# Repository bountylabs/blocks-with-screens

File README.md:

# Blocks With Screens

It's Twitterversary blocks, but with screens and internet. Originally a Fall 2019 Twitter HackWeek project by [@johnboiles](https://github.com/johnboiles), [@magus](https://github.com/magus), [@mikeperiscope](https://github.com/mikeperiscope), [@seanfchan](https://github.com/seanfchan), and [@smartfuse](https://github.com/smartfuse).

## Assembly

### [**Click here to view assembly instructions on YouTube**](https://youtu.be/LxgdhXQPZw0)

Tips, notes & corrections:
* To protect the pins, we're shipping with two of the circuit boards attached to eachother. You'll need to separate these circuit boards before following the instructions above. Just gently pull them apart to separate them. They're hard to break :)
* Some of the boards may have small tabs protruding from the sides which may cause them not to fit in the wooden block. This is a byproduct of the manufacturing process. Clip these tabs off with nail clippers or wire clippers.
* Feel free to ask us on Twitter [@blkswithscreens](https://twitter.com/blkswithscreens) if you have any questions or problems!

## Components

### Blockware

This is the example software that you can run on the blocks. See [blockware/README.md](https://github.com/bountylabs/blocks-with-screens/blob/main/blockware/README.md) for installation instructions and a listing (with gifs!) of the available blockware.

### CAD

This contains the various design files building the block hardware. Most importantly, it contains the [Autodesk Eagle](https://www.autodesk.com/products/eagle/free-download) design files for the 3 PCBs that make up the block. See the [README.md](https://github.com/bountylabs/blocks-with-screens/blob/main/cad/pcb/README.md) in that directory for an overview of the responsibilities of the three different boards.

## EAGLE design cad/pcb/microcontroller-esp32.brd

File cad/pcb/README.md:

# Blocks With Screens PCB Files

## Components

The blocks are made up of 3 components.

### OLED Board

This board is responsible for all the circuitry to drive a SSD1351 OLED display. This design is heavily based on [Adafruit's breakout board](https://github.com/adafruit/Adafruit-1.5inch-Color-OLED-PCB) for the same display.

It consists of a 13V boost regulator to provide the required voltage to drive the OLED, as well as necessary passive components required by the OLED's datasheet.

### Microcontroller Board

This board is a mounting point for the ESP12 microcontroller and the MMA8452Q 3-axis accelerometer. It also has unpopulated pads for a [SparkFun Qwiic](https://www.sparkfun.com/qwiic) connector and a WS2812B RGB LED if you want to add additional functionality.

### USB Board

This board is responsible for:
* Providing a USB serial interface for programming the microcontroller (with automatic reset)
* Providing regulated 3.3V power to the Microcontroller and OLED
* Providing charging circuitry to charge the LiPo battery

This board is based on various Adafruit [LiPo charging boards](https://learn.adafruit.com/adafruit-pro-trinket-lipoly-slash-liion-backpack) and [USB powered boards](https://learn.adafruit.com/introducing-trinket/downloads) with the simplest (by part count) USB-serial chip we could find.

## PCB Hacking

We hope you'll open up your blocks and add new functionality or boards we never even dreamed of.

The pin layout is compatible with the [Wemos D1 Mini](https://docs.wemos.cc/en/latest/d1/d1_mini.html) (available on your usual internet shopping sites) so any shields made for those should work!

There is un unpopulated [SparkFun Qwiic](https://www.sparkfun.com/qwiic) connector on the microcontroller board. If you solder on a Qwiic connector (just a 4-pin JST connector) you can connect your board to any of the dozens of [Qwiic compatible peripherals](https://www.sparkfun.com/qwiic#products) (e.g. sensors, screens, GPS) out there.

There's an unpopulated spot on the Microcontroller board for a WS2812B RGB LED (or similar). This might come in handy if you want to, say, cut a window in the side of your block and trick it out with colors inside. Note that these LEDs will typically initialize to a random color so if you add the LED, but don't use it in your program, it will probably be lit up to a random color.

You could also add PCBs for different microcontrollers, different screens, or maybe even make a USB-C version! This was meant to be modular. Have fun, and share back what you build!

## Manufacturing Boards

We used [OshPark](https://oshpark.com/) for creating our prototype PCBs which we then soldered by hand or in a [reflow oven](https://github.com/UnifiedEngineering/T-962-improvements). We used [PCBWay](https://www.pcbway.com/) to mass manufacture assembled PCBs.

There's an included [script](https://github.com/bountylabs/blocks-with-screens/blob/main/pcb/eagle_to_pcbway.py) for exporting the Eagle PCB files in a bill-of-materials (BOM) format that PCBWay accepts.

## Changelog

### Microcontroller Board V4

* MMA8452QR1 accelerometers are #chipshortage'd. Switch to LIS2DW12

### OLED Board V5

* Revert the revert to go back to VIN for the 13V boost circuit as it didn't seem to have any effect. And this lightens the load on the 3.3V regulator. This is effectively the same design as OLED Board V3.

### USB Board V5

* Turn the battery connector counter-clockwise by 90 degrees to avoid wires hanging off the side of the board and not fitting in the block.

### OLED Board V4

* Revert back to using 3.3V for the 13V boost circuit to hopefully avoid issues I've seen twice now with the OLED screens developing bad vertical lines of pixels. This is what Adafruit does in their board; perhaps there's a reason for it.

### USB Board V4

* Use thicker (power) trace for 3.3V
* Make the USB side slots wider to comply with PCBWay
* Add a JST-SH connector (SM02B-SRSS-TB) for the battery

### Microcontroller Board V3

* Attach 3.3V to the ESP12 (doh!)

### OLED Board V3

* Uses `D4/GPIO2` for `OLED DC` instead of `D1/GPIO5` since that pin is I2C `SCK`.

### Microcontroller Board V2

* Fixed disconnected decoupling capacitor.
* Added optional header for MMA8452QR1 accelerometer.
* Added optional [Qwiic](https://www.sparkfun.com/qwiic) header for SparkFun accessories.
* Added optional [5050 NeoPixel](https://www.adafruit.com/product/1655) pad.

### USB Board V3

* Fix width of power trace going to the switch.

### OLED Board V2

* Uses `D1` for `OLED DC` instead of `D6` (`MISO`) so we don’t have to hack SPI.c for hardware SPI.
* Uses `VIN` for power for the 13V boost (possible this will reduce the flicker, especially during low battery).
* Removed the 3-pin SPI jumper since we didn’t use it.
* Move all the screen capacitors closer to the screen connector (even smaller chance of reducing flicker)

### USB Board V2

* Removed oscillator and move to using the `CH340C` instead of `CH340G` USB-UART chip.
* Connect `VCC` on the `CH340C` chip (fix error from V1).
* Move most parts to the front of the board for easier manufacturing.
* Add an optional on LED.
* Add pads for a switch.

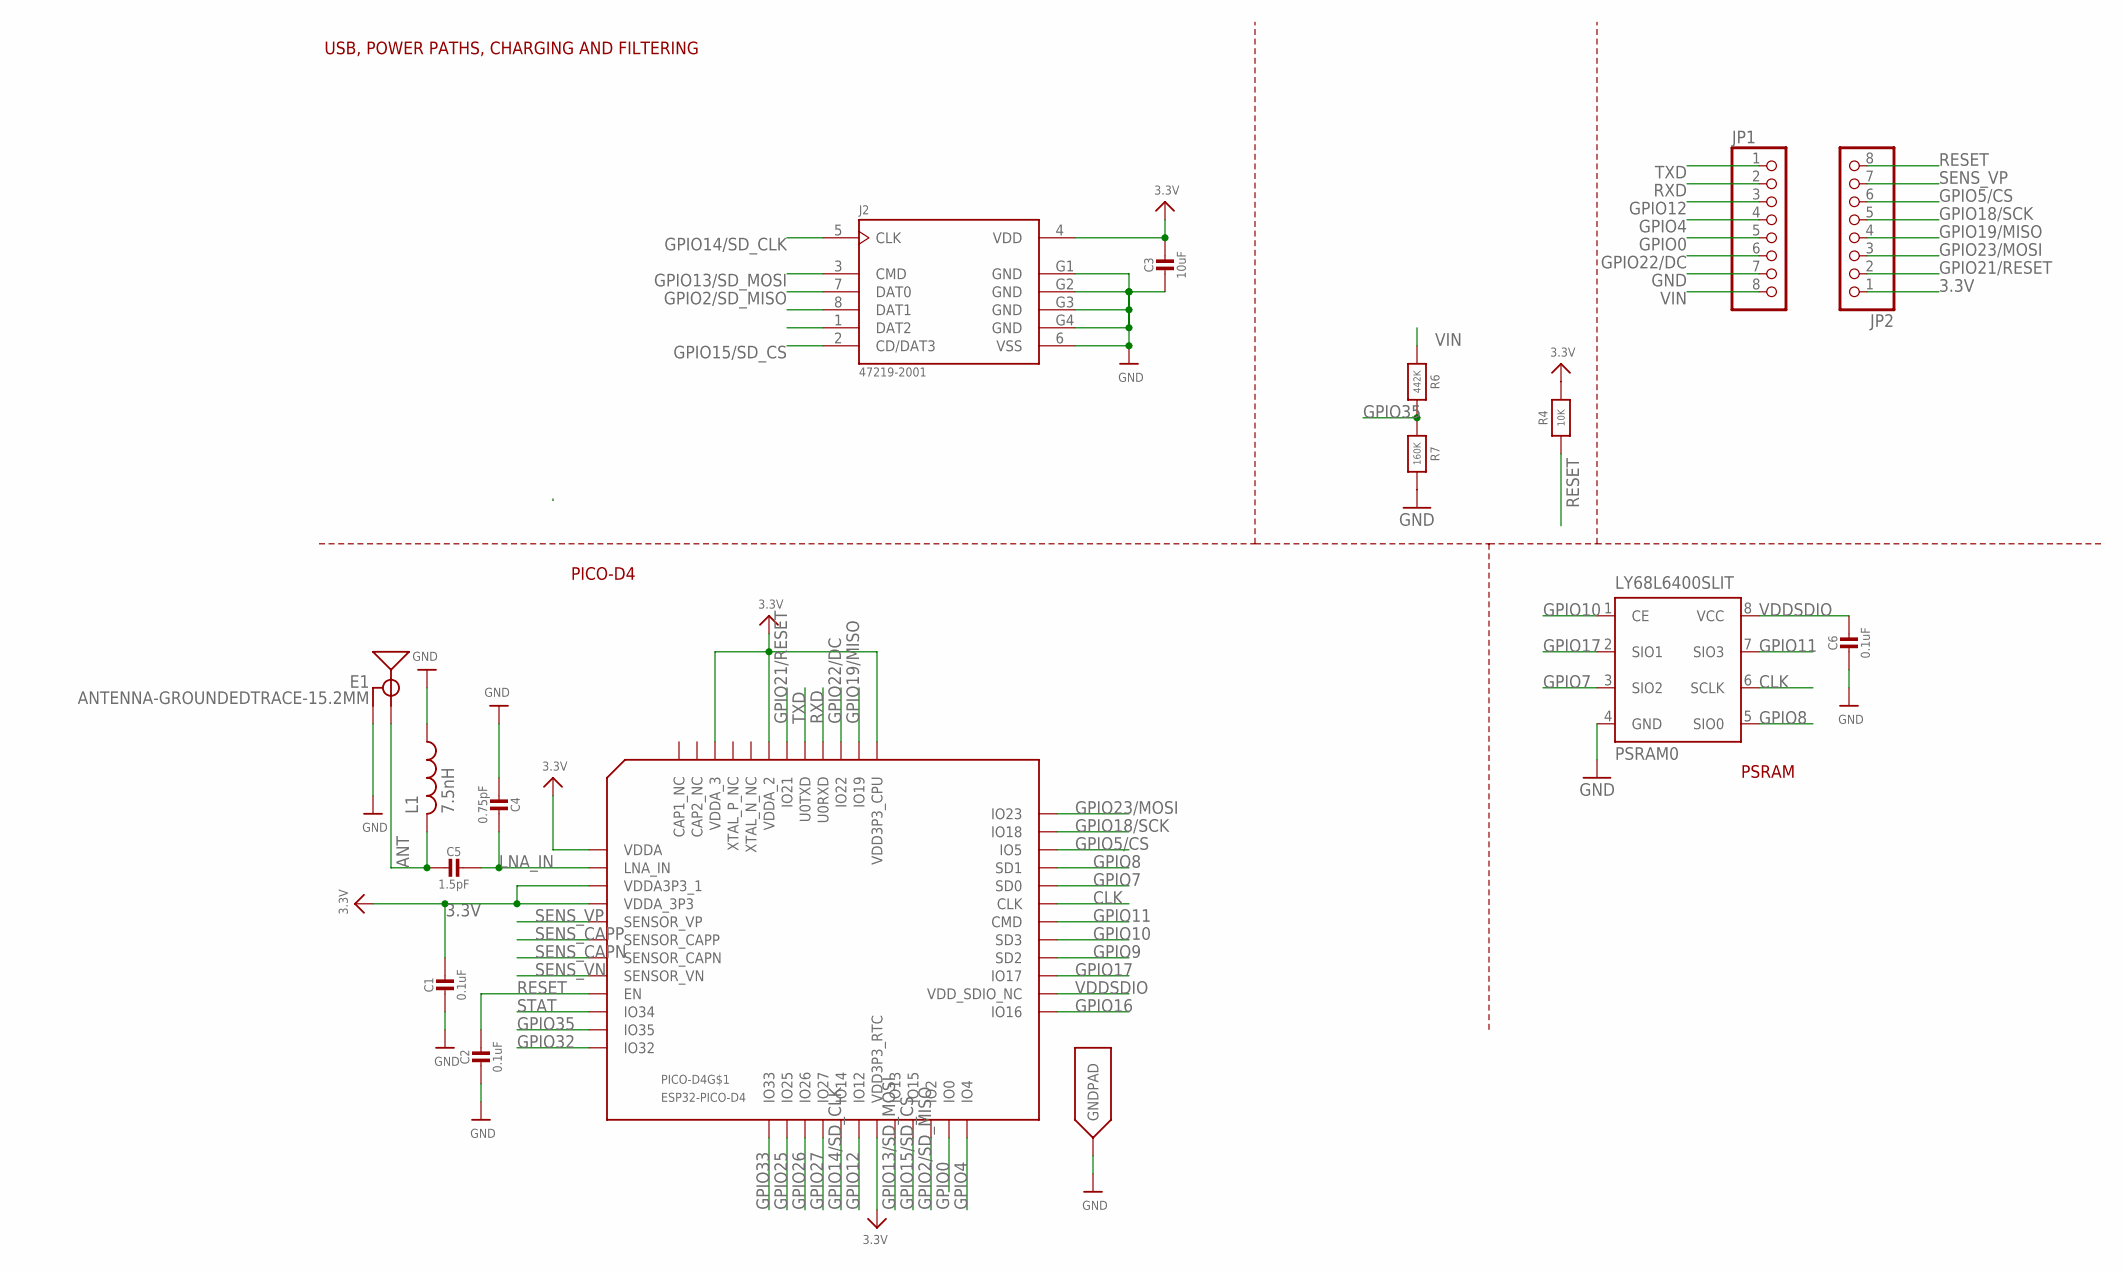
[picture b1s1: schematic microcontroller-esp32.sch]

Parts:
C1, C2, C6: 0.1uF; _0402MP
C3: 10uF; _0402MP
C4: 0.75pF; _0402MP
C5: 1.5pF; _0402MP
E1: ANTENNA-GROUNDEDTRACE-15.2MM; TRACE_ANTENNA_2.4GHZ_15.2MM
J2: 47219-2001; MOLEX_47219-2001
JP1, JP2: PINHD-1X8CLEANBIG; 1X08-CLEANBIG; MPN 83-15410
L1: 7.5nH; RESC0402_N
LY68L6400SLIT: PSRAM0; SOP8
PICO-D4: ESP32-PICO-D4; PICO-D4-QFN48
R4: 10K; _0402MP
R6: 442K; _0402MP
R7: 160K; _0402MP

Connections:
3.3V: C1.1, C3.1, J2.4 (VDD), JP2.1, PICO-D4.1 (VDDA), PICO-D4.3 (VDDA3P3_1), PICO-D4.4 (VDDA_3P3), PICO-D4.19 (VDD3P3_RTC), PICO-D4.37 (VDD3P3_CPU), PICO-D4.43 (VDDA_2), PICO-D4.46 (VDDA_3), R4.2
ANT: C5.2, E1.ANT (SIGNAL), L1.2
CLK: LY68L6400SLIT.6 (SCLK), PICO-D4.31 (CLK)
GND: C1.2, C2.2, C3.2, C4.2, C6.2, E1.GND, J2.6 (VSS), J2.G1 (GND), J2.G2 (GND), J2.G3 (GND), J2.G4 (GND), JP1.7, L1.1, LY68L6400SLIT.4 (GND), PICO-D4.EXP (GNDPAD), R7.2
GPIO0: JP1.5, PICO-D4.23 (IO0)
GPIO2/SD_MISO: J2.7 (DAT0), PICO-D4.22 (IO2)
GPIO4: JP1.4, PICO-D4.24 (IO4)
GPIO5/CS: JP2.6, PICO-D4.34 (IO5)
GPIO7: LY68L6400SLIT.3 (SIO2), PICO-D4.32 (SD0)
GPIO8: LY68L6400SLIT.5 (SIO0), PICO-D4.33 (SD1)
GPIO9: PICO-D4.28 (SD2)
GPIO10: LY68L6400SLIT.1 (CE), PICO-D4.29 (SD3)
GPIO11: LY68L6400SLIT.7 (SIO3), PICO-D4.30 (CMD)
GPIO12: JP1.3, PICO-D4.18 (IO12)
GPIO13/SD_MOSI: J2.3 (CMD), PICO-D4.20 (IO13)
GPIO14/SD_CLK: J2.5 (CLK), PICO-D4.17 (IO14)
GPIO15/SD_CS: J2.2 (CD/DAT3), PICO-D4.21 (IO15)
GPIO16: PICO-D4.25 (IO16)
GPIO17: LY68L6400SLIT.2 (SIO1), PICO-D4.27 (IO17)
GPIO18/SCK: JP2.5, PICO-D4.35 (IO18)
GPIO19/MISO: JP2.4, PICO-D4.38 (IO19)
GPIO21/RESET: JP2.2, PICO-D4.42 (IO21)
GPIO22/DC: JP1.6, PICO-D4.39 (IO22)
GPIO23/MOSI: JP2.3, PICO-D4.36 (IO23)
GPIO25: PICO-D4.14 (IO25)
GPIO26: PICO-D4.15 (IO26)
GPIO27: PICO-D4.16 (IO27)
GPIO32: PICO-D4.12 (IO32)
GPIO33: PICO-D4.13 (IO33)
GPIO35: PICO-D4.11 (IO35), R6.2, R7.1
LNA_IN: C4.1, C5.1, PICO-D4.2 (LNA_IN)
RESET: C2.1, JP2.8, PICO-D4.9 (EN), R4.1
RXD: JP1.2, PICO-D4.40 (U0RXD)
SENS_CAPN: PICO-D4.7 (SENSOR_CAPN)
SENS_CAPP: PICO-D4.6 (SENSOR_CAPP)
SENS_VN: PICO-D4.8 (SENSOR_VN)
SENS_VP: JP2.7, PICO-D4.5 (SENSOR_VP)
STAT: PICO-D4.10 (IO34)
TXD: JP1.1, PICO-D4.41 (U0TXD)
VDDSDIO: C6.1, LY68L6400SLIT.8 (VCC), PICO-D4.26 (VDD_SDIO_NC)
VIN: JP1.8, R6.1

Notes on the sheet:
USB, POWER PATHS, CHARGING AND FILTERING
PICO-D4
PSRAM

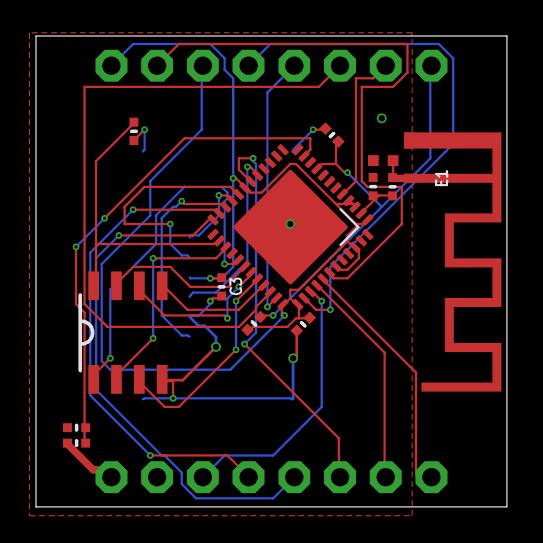
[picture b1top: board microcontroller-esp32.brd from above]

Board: 4 copper layers, 26.2 x 26.2 mm, 16 parts (1 on the bottom side), 30 nets.

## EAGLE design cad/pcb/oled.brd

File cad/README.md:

# CAD Files

This contains the various design files for the mechanical components of the blocks.

## Parts List
* Assembled PCBs (See the README.md in the `pcb` directory in the repository for more details)
  * USB board
  * Microcontroller board
  * OLED board
* 1.5” SSD1351 128x128 OLED screen
* 240mAh 602025 LiPo battery with JST-SH connector
* Laser-cut wood “puzzle” blocks (5 separate pieces that fit together)
* Laser cut paper spacers (for friction fit and alignment)

## Components

### PCBs

The most important part of the block! The `pcb` directory contains the [Autodesk Eagle](https://www.autodesk.com/products/eagle/free-download) design files for the 3 PCBs that make up the block. See the [README.md](https://github.com/bountylabs/blocks-with-screens/blob/main/cad/pcb/README.md) in that directory for an overview of the responsibilities of the three different boards.

### Laser-cut Wood “Puzzle” Blocks

These are the laser-cuttable sides and back of the block. Since these need to fit together with only friction, the design may need to be adjusted based on the laser being used. Designs are included for a 0.23mm kerf laser as well as ones that worked well on @johnboiles's GlowForge. The `puzzleblock.f3d` (Fusion 360) file has the original designs.

### Laser-cut Paper Spacers

These help hold the PCBs inside the block and also helps center them inside the block. These should be cut out of 110 lb card stock paper. The laser width doesn’t matter here since paper bends.

### Block With Screen F3Z File

This Fusion 360 file has all of the components modeled in one place. Used mostly for neat visualizations like the assembly video. Also very useful to visualize the internal spacing when changing PCB components placements. This also contains the original design for the paper spacers.

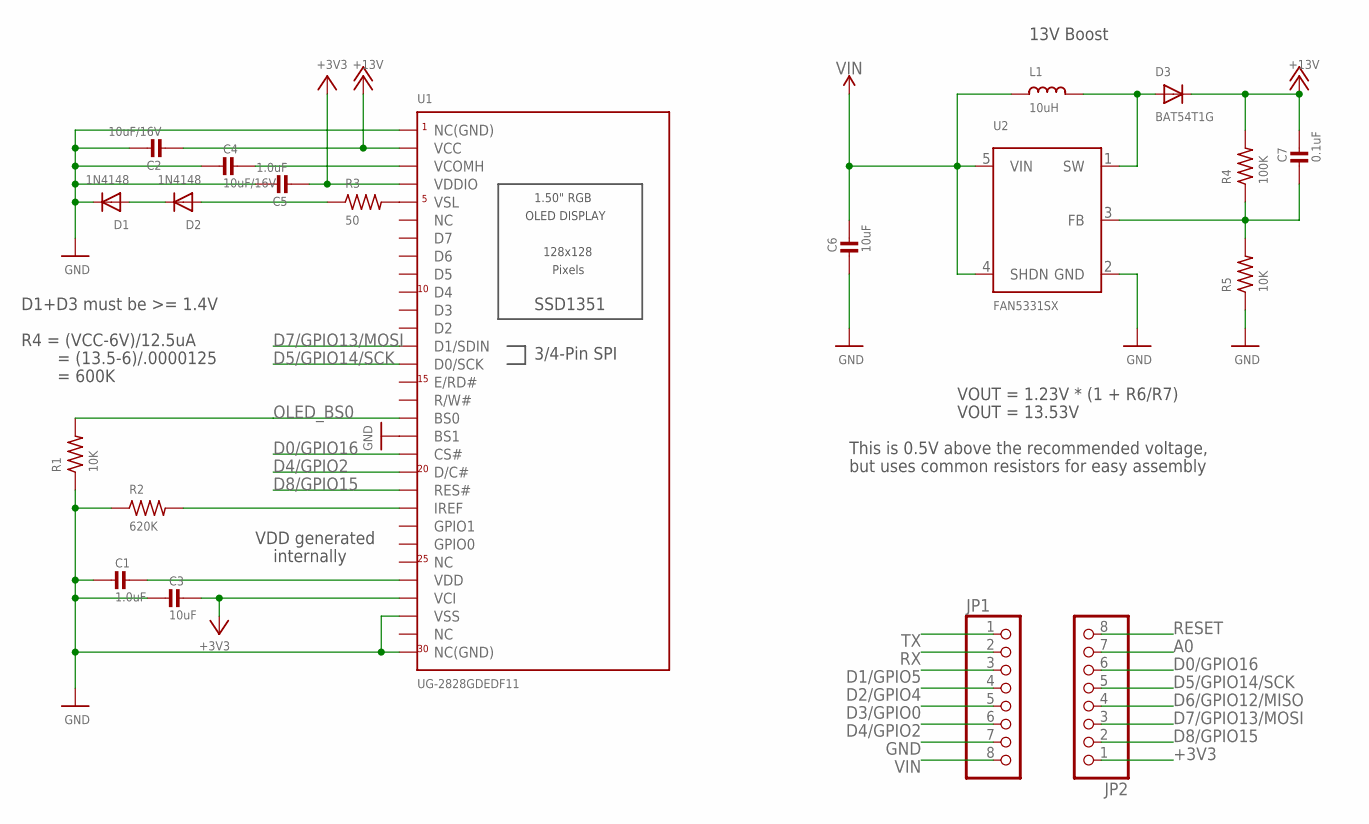
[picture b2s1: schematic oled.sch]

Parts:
C1, C5: 1.0uF; 0805; MPN C0805C105K4RAC7210
C2, C4: 10uF/16V; 0805; MPN CL21A106KOQNNNE
C3, C6: 10uF; 0805; MPN CL21A106KOQNNNE
C7: 0.1uF; 0805; MPN C0805C104M3RACTU
D1, D2: 1N4148; SOD-323; MPN 1N4148WS-E3-08
D3: BAT54T1G; SOD-123; MPN BAT54T1G
JP1, JP2: PINHD-1X8CLEANBIG; 1X08-CLEANBIG; MPN C124381
L1: 10uH; INDUCTOR_1007; MPN L0805R100MPWRT
R1, R5: 10K; R0805; MPN CRCW080510K0FKEAC
R2: 620K; R0805; MPN 0805W8F6203T5E
R3: 50; R0805; MPN CRCW080550R0FKTA
R4: 100K; R0805; MPN CR0805AFX-1003EAS
U1: UG-2828GDEDF11; FPC_XF2M-3015-1A; MPN XF2M-3015-1A
U2: FAN5331SX; SOT23-5@1; MPN FAN5331SX

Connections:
13V: C2.2, C7.1, D3.C, R4.2, U1.P$29 (VCC)
+3V3: C3.1, C5.2, JP2.1, U1.P$4 (VCI), U1.P$27 (VDDIO)
A0: JP2.7
D0/GPIO16: JP2.6, U1.P$12 (CS#)
D1/GPIO5: JP1.3
D2/GPIO4: JP1.4
D3/GPIO0: JP1.5
D4/GPIO2: JP1.6, U1.P$11 (D/C#)
D5/GPIO14/SCK: JP2.5, U1.P$17 (D0/SCK)
D6/GPIO12/MISO: JP2.4
D7/GPIO13/MOSI: JP2.3, U1.P$18 (D1/SDIN)
D8/GPIO15: JP2.2, U1.P$10 (RES#)
GND: C1.2, C2.1, C3.2, C4.2, C5.1, C6.2, D1.C, JP1.7, R1.1, R2.1, R5.1, U1.P$1 (NC(GND)), U1.P$3 (VSS), U1.P$13 (BS1), U1.P$30 (NC(GND)), U2.2 (GND)
IREF: R2.2, U1.P$9 (IREF)
unnamed: C1.1, U1.P$5 (VDD)
unnamed: D3.A, L1.P$2 (2), U2.1 (SW)
unnamed: R3.2, U1.P$26 (VSL)
unnamed: D2.A, R3.1
unnamed: C7.2, R4.1, R5.2, U2.3 (FB)
unnamed: D1.A, D2.C
OLED_BS0: R1.2, U1.P$14 (BS0)
RESET: JP2.8
RX: JP1.2
TX: JP1.1
VCOMH: C4.1, U1.P$28 (VCOMH)
VIN: C6.1, JP1.8, L1.P$1 (1), U2.4 (SHDN), U2.5 (VIN)

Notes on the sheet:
VOUT = 1.23V * (1 + R6/R7)
VOUT = 13.53V
This is 0.5V above the recommended voltage,
but uses common resistors for easy assembly
13V Boost
R4 = (VCC-6V)/12.5uA
= (13.5-6)/.0000125
= 600K
D1+D3 must be >= 1.4V
VDD generated
internally

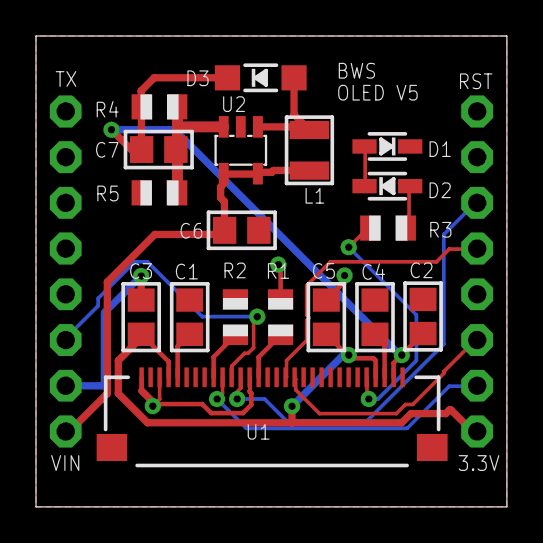
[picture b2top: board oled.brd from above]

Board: 2 copper layers, 26.2 x 26.2 mm, 21 parts (1 on the bottom side), 18 nets.

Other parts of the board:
U$1: TWITTER5MM

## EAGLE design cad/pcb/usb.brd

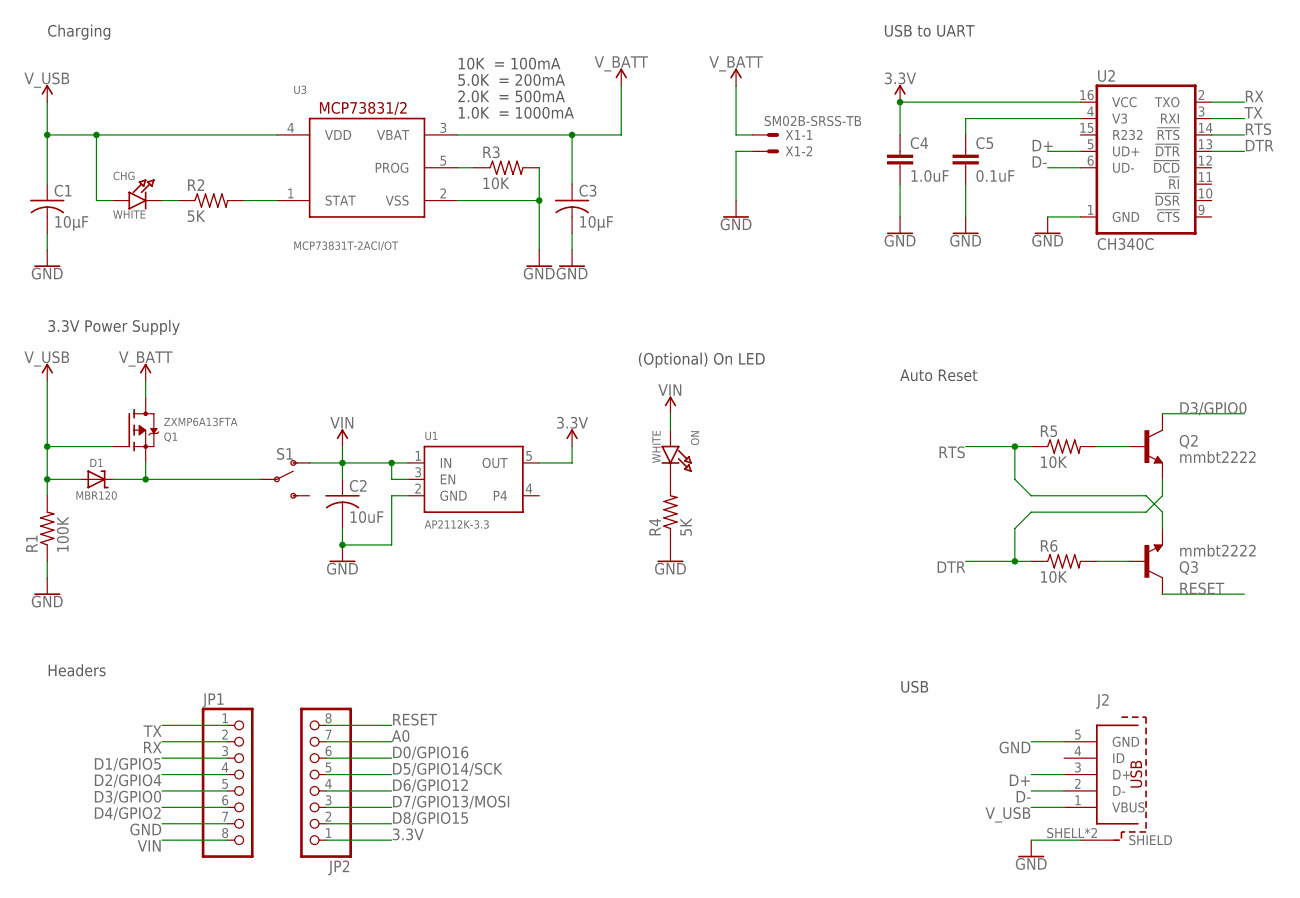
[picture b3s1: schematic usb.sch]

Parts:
C1, C3: 10µF; C0805; MPN CL21A106KPFNNNE
C2: 10uF; C0805; MPN CL21A106KPFNNNE
C4: 1.0uF; 0805; MPN C0805C105K4RAC7210
C5: 0.1uF; 0805; MPN C0805C104M3RACTU
CHG: WHITE; CHIPLED_0805_NOOUTLINE; MPN NCD0805W2
D1: MBR120; SOD-123; MPN MBR120ESFT1G
J2: 614105150621; MPN U-D-M5DD-W-1
JP1, JP2: PINHD-1X8CLEANBIG; 1X08-CLEANBIG; MPN C27438
ON: WHITE; CHIPLED_0805_NOOUTLINE; MPN NCD0805W2
Q1: ZXMP6A13FTA; SOT23-R; MPN ZXMP6A13FTA
Q2, Q3: mmbt2222; SOT23-3; MPN MMBT2222A-G
R1: 100K; R0805; MPN 0805W8F1003T5E
R2, R4: 5K; R0805; MPN 0805W8F4871T5E
R3: 10K; R0805; MPN CRCW080510K0FKEAC
R5, R6: 10K; R0603; MPN RC0603FR-0710KL
S1: SWITCH-SPDT-SMD-AYZ0202; SWITCH_DPDT_SMD_AYZ0202; MPN AYZ0202AGRLC
U1: AP2112K-3.3; SOT23-5; MPN AP2112K-3.3
U2: CH340C; SO016; MPN CH340C
U3: MCP73831T-2ACI/OT; SOT23-5L; MPN MCP73831T-2ACI/OT
X1: SM02B-SRSS-TB; MPN SM02B-SRSS-TB

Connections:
3.3V: C4.1, JP2.1, U1.5 (OUT), U2.16 (VCC)
A0: JP2.7
D0/GPIO16: JP2.6
D1/GPIO5: JP1.3
D2/GPIO4: JP1.4
D3/GPIO0: JP1.5, Q2.3 (C)
D4/GPIO2: JP1.6
D5/GPIO14/SCK: JP2.5
D6/GPIO12: JP2.4
D7/GPIO13/MOSI: JP2.3
D8/GPIO15: JP2.2
D+: J2.3 (D+), U2.5 (UD+)
D-: J2.2 (D-), U2.6 (UD-)
DTR: Q2.2 (E), R6.1, U2.13 (!DTR)
GND: C1.2, C2.2, C3.2, C4.2, C5.2, J2.5 (GND), J2.SHELL (SHIELD), J2.SHELL1 (SHIELD), JP1.7, R1.1, R3.2, R4.1, U1.2 (GND), U2.1 (GND), U3.2 (VSS), X1.2
unnamed: CHG.C, R2.1
unnamed: C5.1, U2.4 (V3)
unnamed: ON.C, R4.2
unnamed: R2.2, U3.1 (STAT)
unnamed: D1.C, Q1.2 (S), S1.5
unnamed: R3.1, U3.5 (PROG)
unnamed: Q3.1 (B), R6.2
unnamed: Q2.1 (B), R5.2
RESET: JP2.8, Q3.3 (C)
RTS: Q3.2 (E), R5.1, U2.14 (!RTS)
RX: JP1.2, U2.2 (TXO)
TX: JP1.1, U2.3 (RXI)
VIN: C2.1, JP1.8, ON.A, S1.6 (O), U1.1 (IN), U1.3 (EN)
V_BATT: C3.1, Q1.3 (D), U3.3 (VBAT), X1.1
V_USB: C1.1, CHG.A, D1.A, J2.1 (VBUS), Q1.1 (G), R1.2, U3.4 (VDD)

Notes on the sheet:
10K = 100mA
5.0K = 200mA
2.0K = 500mA
1.0K = 1000mA
Charging
3.3V Power Supply
Headers
USB to UART
Auto Reset
USB
(Optional) On LED

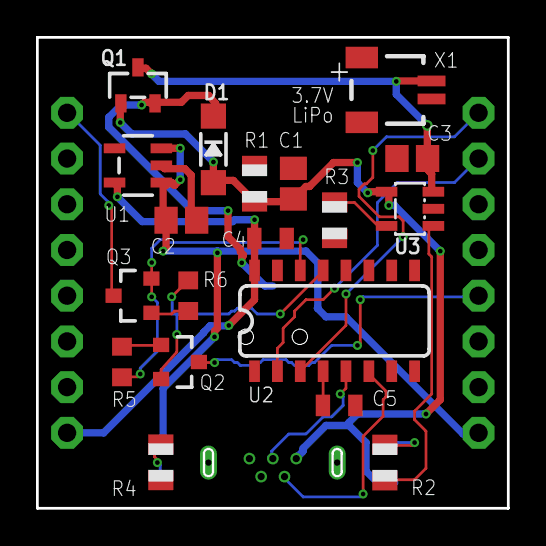
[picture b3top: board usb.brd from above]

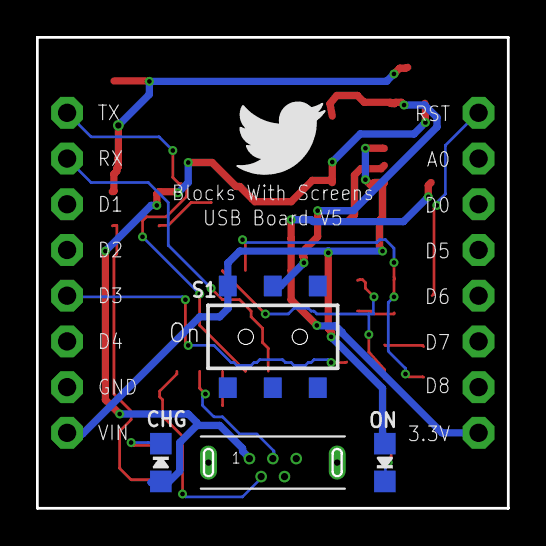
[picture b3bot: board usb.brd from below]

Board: 2 copper layers, 26.2 x 26.2 mm, 26 parts (5 on the bottom side), 21 nets.

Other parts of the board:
U$1: TWITTER5MM

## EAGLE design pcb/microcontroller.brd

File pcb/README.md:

# Blocks With Screens PCB Files

## Components

The blocks are made up of 3 components.

### OLED Board

This board is responsible for all the circuitry to drive a SSD1351 OLED display. This design is heavily based on [Adafruit's breakout board](https://github.com/adafruit/Adafruit-1.5inch-Color-OLED-PCB) for the same display.

It consists of a 13V boost regulator to provide the required voltage to drive the OLED, as well as necessary passive components required by the OLED's datasheet.

### Microcontroller Board

This board is a mounting point for the ESP12 microcontroller and the MMA8452Q 3-axis accelerometer. It also has unpopulated headers for a [SparkFun Qwiic](https://www.sparkfun.com/qwiic) connector and a WS2812B RGB LED if you want to add additional functionality.

### USB Board

This board is responsible for:
* Providing a USB serial interface for programming the microcontroller (with automatic reset)
* Providing regulated 3.3V power to the Microcontroller and OLED
* Providing charging circuitry to charge the LiPo battery

This board is based on various Adafruit [LiPo charging boards](https://learn.adafruit.com/adafruit-pro-trinket-lipoly-slash-liion-backpack) and [USB powered boards](https://learn.adafruit.com/introducing-trinket/downloads) with the simplest (by part count) USB-serial chip we could find.

## PCB Hacking

We hope you'll open up your blocks and add new functionality or boards we never even dreamed of.

The pin layout is compatible with the [Wemos D1 Mini](https://docs.wemos.cc/en/latest/d1/d1_mini.html) (available on your usual internet shopping sites) so any shields made for those should work!

There is un unpopulated [SparkFun Qwiic](https://www.sparkfun.com/qwiic) connector on the microcontroller board. If you solder on a Qwiic connector (just a 4-pin JST connector) you can connect your board to any of the dozens of [Qwiic compatible peripherals](https://www.sparkfun.com/qwiic#products) (e.g. sensors, screens, GPS) out there.

There's an unpopulated spot on the Microcontroller board for a WS2812B RGB LED (or similar). This might come in handy if you want to, say, cut a window in the side of your block and trick it out with colors inside. Note that these LEDs will typically initialize to a random color so if you add the LED, but don't use it in your program, it will probably be lit up to a random color.

You could also add PCBs for different microcontrollers, different screens, or maybe even make a USB-C version! This was meant to be modular. Have fun, and share back what you build!

## Manufacturing Boards

We used [OshPark](https://oshpark.com/) for creating our prototype PCBs which we then soldered by hand or in a [reflow oven](https://github.com/UnifiedEngineering/T-962-improvements). We used [PCBWay](https://www.pcbway.com/) to mass manufacture assembled PCBs.

There's an included [script](https://github.com/bountylabs/blocks-with-screens/blob/main/pcb/eagle_to_pcbway.py) for exporting the Eagle PCB files in a bill-of-materials (BOM) format that PCBWay accepts.

## Changelog

### USB Board V5

* Turn the battery connector counter-clockwise by 90 degrees to avoid wires hanging off the side of the board and not fitting in the block.

### OLED Board V4

* Revert back to using 3.3V for the 13V boost circuit to hopefully avoid issues I've seen twice now with the OLED screens developing bad vertical lines of pixels. This is what Adafruit does in their board; perhaps there's a reason for it.

### USB Board V4

* Use thicker (power) trace for 3.3V
* Make the USB side slots wider to comply with PCBWay
* Add a JST-SH connector (SM02B-SRSS-TB) for the battery

### Microcontroller Board V3

* Attach 3.3V to the ESP12 (doh!)

### OLED Board V3

* Uses `D4/GPIO2` for `OLED DC` instead of `D1/GPIO5` since that pin is I2C `SCK`.

### Microcontroller Board V2

* Fixed disconnected decoupling capacitor.
* Added optional header for MMA8452QR1 accelerometer.
* Added optional [Qwiic](https://www.sparkfun.com/qwiic) header for SparkFun accessories.
* Added optional [5050 NeoPixel](https://www.adafruit.com/product/1655) pad.

### USB Board V3

* Fix width of power trace going to the switch.

### OLED Board V2

* Uses `D1` for `OLED DC` instead of `D6` (`MISO`) so we don’t have to hack SPI.c for hardware SPI.
* Uses `VIN` for power for the 13V boost (possible this will reduce the flicker, especially during low battery).
* Removed the 3-pin SPI jumper since we didn’t use it.
* Move all the screen capacitors closer to the screen connector (even smaller chance of reducing flicker)

### USB Board V2

* Removed oscillator and move to using the `CH340C` instead of `CH340G` USB-UART chip.
* Connect `VCC` on the `CH340C` chip (fix error from V1).
* Move most parts to the front of the board for easier manufacturing.
* Add an optional on LED.
* Add pads for a switch.

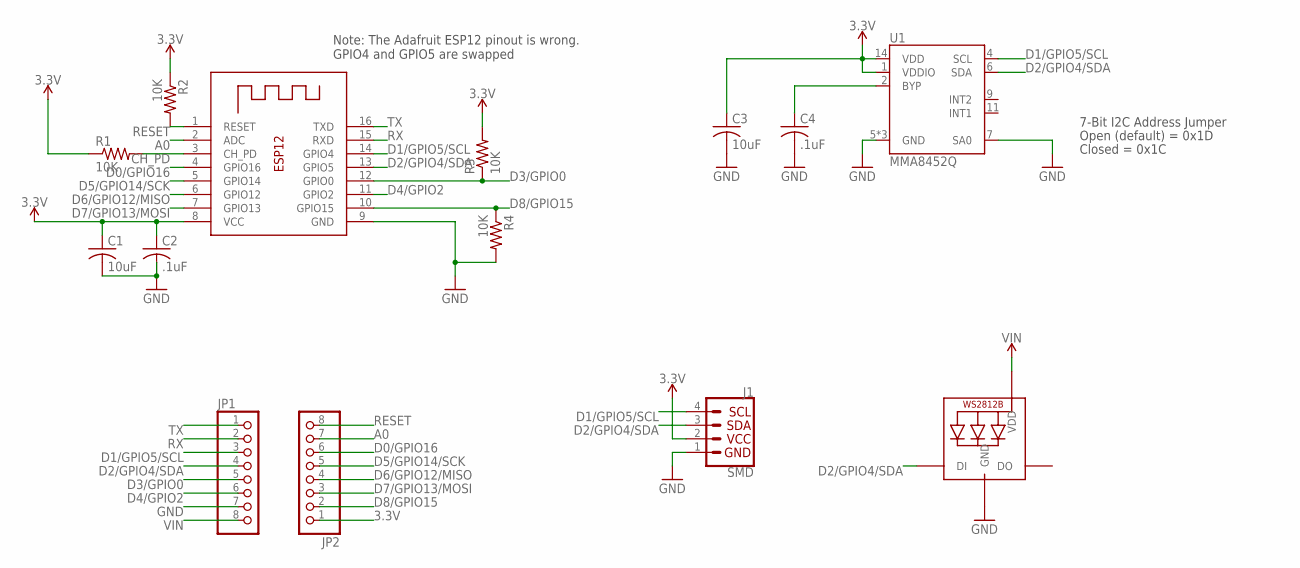
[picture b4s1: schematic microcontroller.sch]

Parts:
C1, C3: 10uF; C0805; MPN LMK212BJ106KG-T
C2, C4: .1uF; C0805; MPN C0805C104M3RACTU
J1: SMD; 1X04_1MM_RA; MPN PRT-14417
JP1, JP2: PINHD-1X8CLEANBIG; 1X08-CLEANBIG; MPN 8Fx1L-254mm
LED1: WS2812B5050; WS2812B; MPN 1655
R1, R2, R3, R4: 10K; R0805; MPN CRCW080510K0FKEAC
U1: MMA8452Q; QFN-16_0.5MM; MPN MMA8452QR1
X1: ESP-12; MPN ESP12

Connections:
3.3V: C1.1, C2.1, C3.1, J1.2 (VCC), JP2.1, R1.1, R2.1, R3.2, U1.1 (VDDIO), U1.14 (VDD), X1.8 (VCC)
A0: JP2.7, X1.2 (ADC)
BYP: C4.1, U1.2 (BYP)
CH_PD: R1.2, X1.3 (CH_PD)
D0/GPIO16: JP2.6, X1.4 (GPIO16)
D1/GPIO5/SCL: J1.4 (SCL), JP1.3, U1.4 (SCL), X1.14 (GPIO4)
D2/GPIO4/SDA: J1.3 (SDA), JP1.4, LED1.4-DIN (DI), U1.6 (SDA), X1.13 (GPIO5)
D3/GPIO0: JP1.5, R3.1, X1.12 (GPIO0)
D4/GPIO2: JP1.6, X1.11 (GPIO2)
D5/GPIO14/SCK: JP2.5, X1.5 (GPIO14)
D6/GPIO12/MISO: JP2.4, X1.6 (GPIO12)
D7/GPIO13/MOSI: JP2.3, X1.7 (GPIO13)
D8/GPIO15: JP2.2, R4.1, X1.10 (GPIO15)
GND: C1.2, C2.2, C3.2, C4.2, J1.1 (GND), JP1.7, LED1.3-GND (GND), R4.2, U1.5 (GND), U1.7 (SA0), U1.10 (GND), U1.12 (GND), X1.9 (GND)
RESET: JP2.8, R2.2, X1.1 (RESET)
RX: JP1.2, X1.15 (RXD)
TX: JP1.1, X1.16 (TXD)
VIN: JP1.8, LED1.1-VDD (VDD)

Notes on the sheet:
7-Bit I2C Address Jumper
Closed = 0x1C
Open (default) = 0x1D
Note: The Adafruit ESP12 pinout is wrong. GPIO4 and GPIO5 are swapped

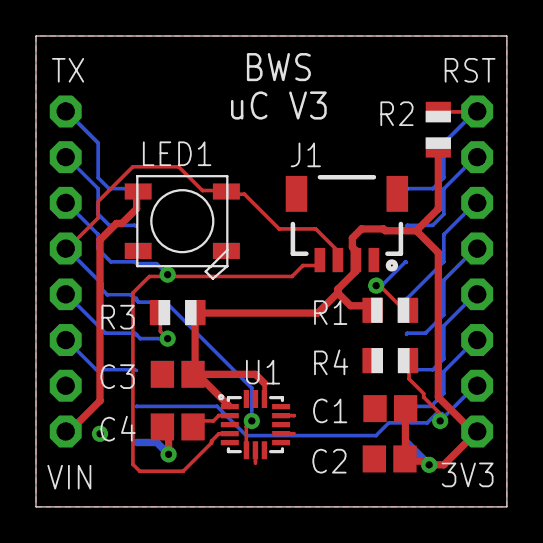
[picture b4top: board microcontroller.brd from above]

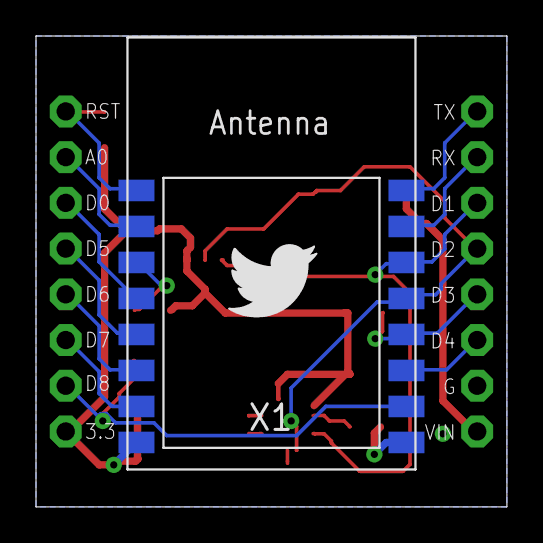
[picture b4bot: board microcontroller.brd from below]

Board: 2 copper layers, 26.2 x 26.2 mm, 15 parts (4 on the bottom side), 18 nets.

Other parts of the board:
U$1: TWITTER5MM

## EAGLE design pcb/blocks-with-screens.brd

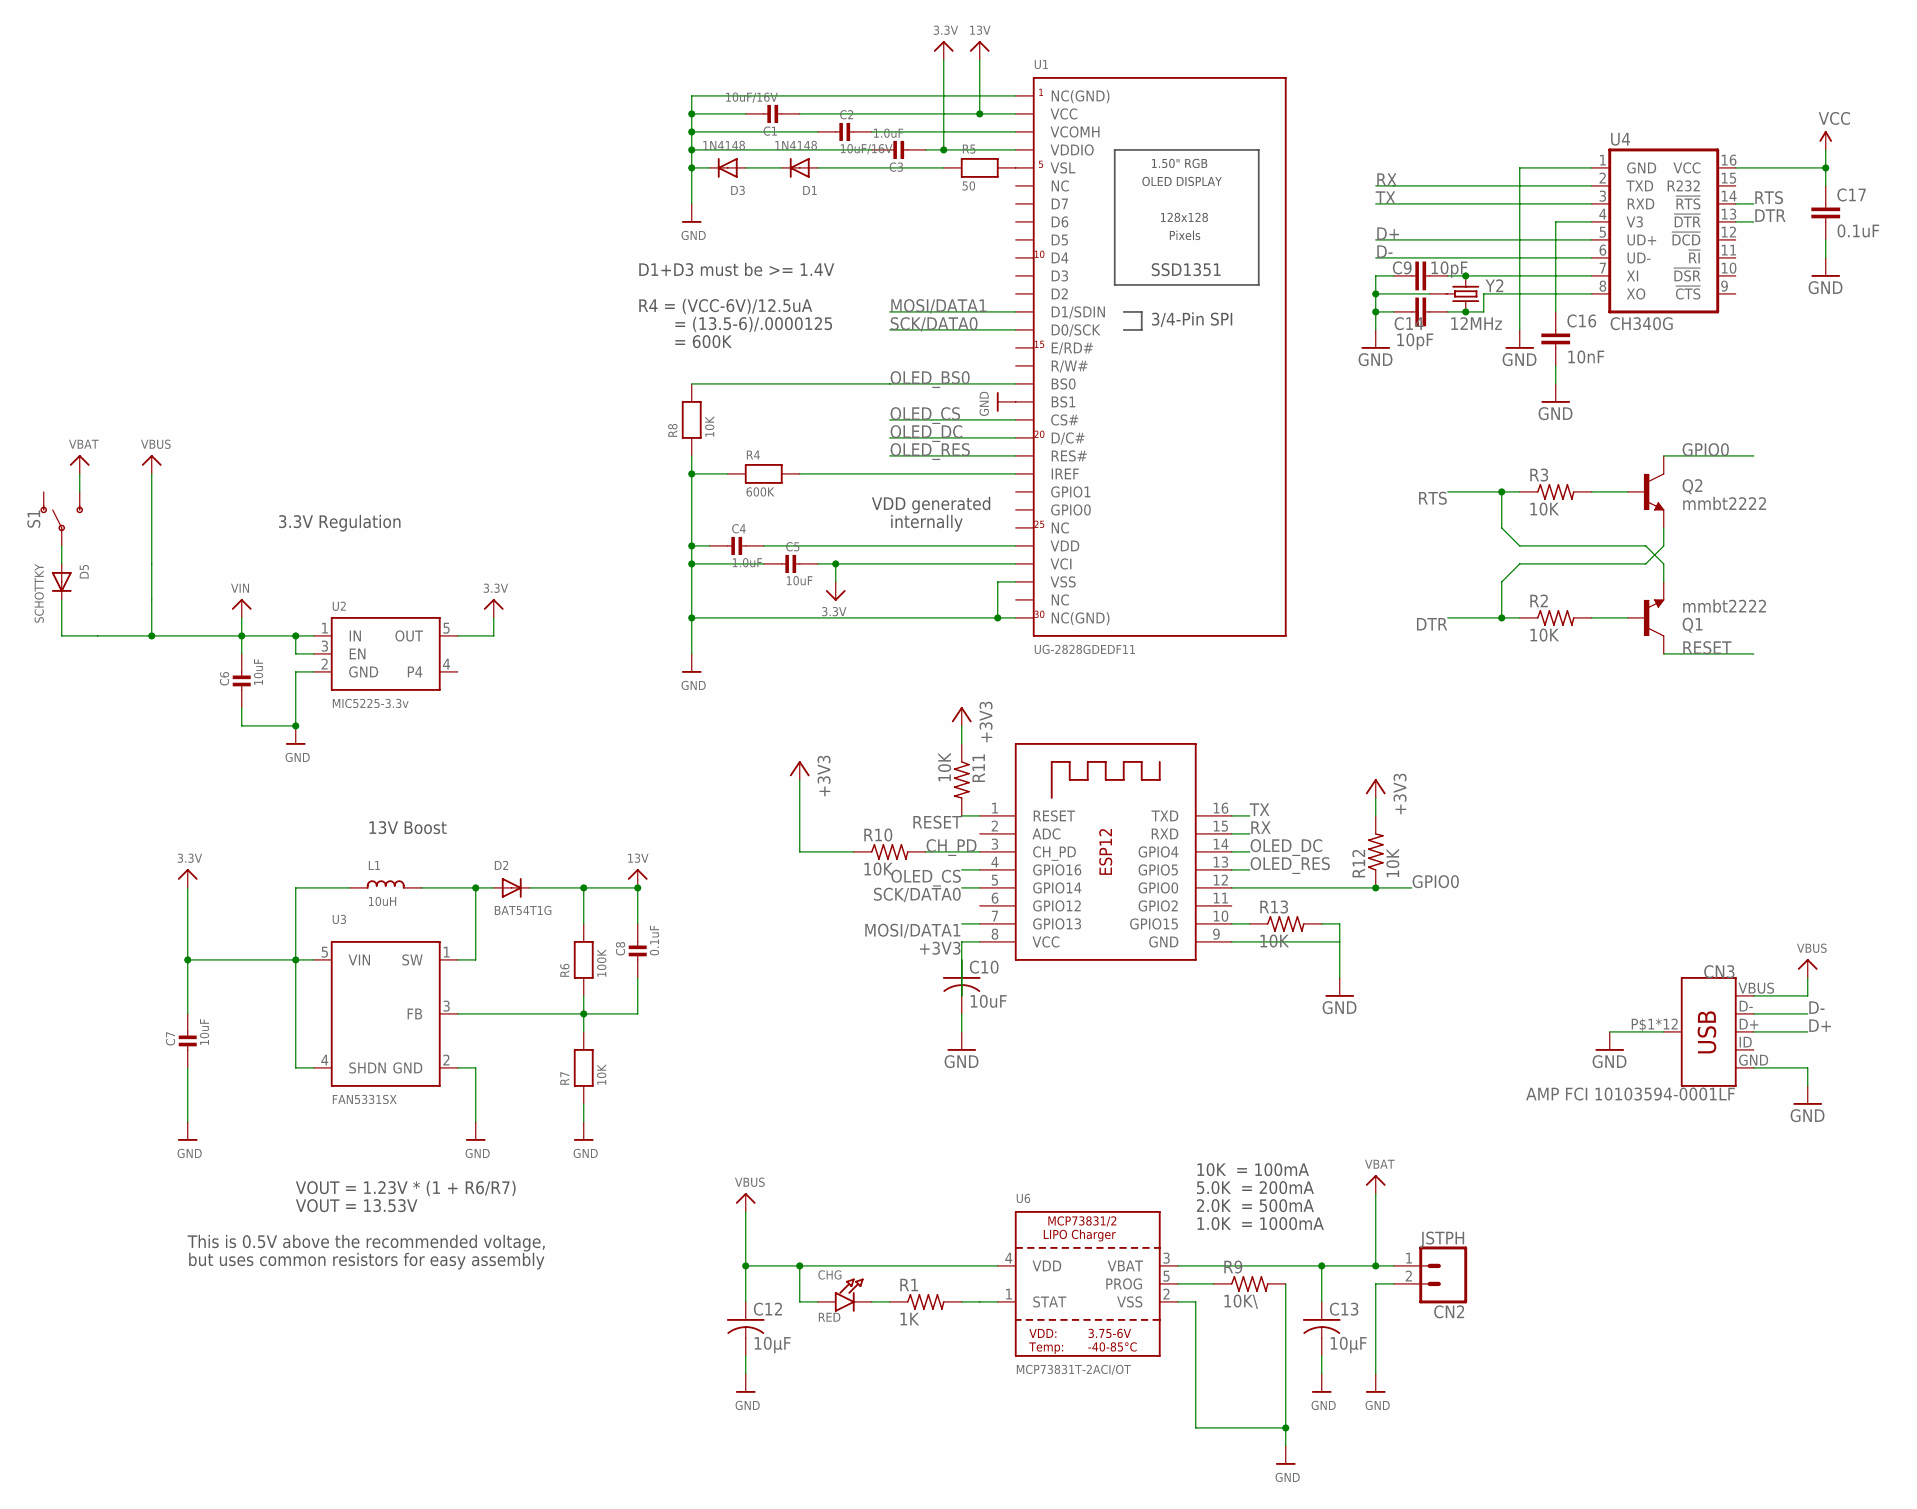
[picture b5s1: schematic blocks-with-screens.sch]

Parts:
C1, C2: 10uF/16V; 0805
C3, C4: 1.0uF; 0805
C5, C6, C7: 10uF; 0805
C8: 0.1uF; 0805
C9, C14: 10pF; 0603-CAP
C10: 10uF; C0805
C12, C13: 10µF; C0805
C16: 10nF; 0603-CAP
C17: 0.1uF; 0603-CAP
CHG: RED; CHIPLED_0805_NOOUTLINE
CN2: JSTPH; 1X02
CN3: AMP FCI 10103594-0001LF; USB-MICROB-PTH
D1, D3: 1N4148; SOD-323
D2: BAT54T1G; SOD-123
D5: SCHOTTKY; SOD-123FL
L1: 10uH; INDUCTOR_1007
Q1, Q2: mmbt2222; SOT23-3
R1: 1K; R0805
R2, R3: 10K; R0603
R4: 600K; 0805
R5: 50; 0805
R6: 100K; 0805
R7, R8: 10K; 0805
R9: 10K\; R0805
R10, R11, R12, R13: 10K; R0805
S1: SWITCH-SPDT-SMD-RIGHT-ANGLE; SWITCH_SPST_SMD_A
U1: UG-2828GDEDF11; FPC_XF2M-3015-1A
U2: MIC5225-3.3v; SOT23-5
U3: FAN5331SX; SOT23-5@1
U4: CH340G; SO016
U6: MCP73831T-2ACI/OT; SOT23-5
X1: ESP-12
Y2: 12MHz; CRYSTAL-SMD-3.2X2.5

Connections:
3.3V: C3.2, C5.1, C7.1, L1.P$1 (1), U1.P$4 (VCI), U1.P$27 (VDDIO), U2.5 (OUT), U3.4 (SHDN), U3.5 (VIN)
13V: C1.2, C8.1, D2.C, R6.2, U1.P$29 (VCC)
+3V3: C10.1, R10.1, R11.1, R12.2, X1.8 (VCC)
CH_PD: R10.2, X1.3 (CH_PD)
D+: CN3.D+, U4.5 (UD+)
D-: CN3.D-, U4.6 (UD-)
DTR: Q2.2 (E), R2.1, U4.13 (!DTR)
GND: C1.1, C2.2, C3.1, C4.2, C5.2, C6.2, C7.2, C9.1, C10.2, C12.2, C13.2, C14.1, C16.2, C17.2, CN2.2, CN3.GND, CN3.P$1 (SHIELD), CN3.P$2 (SHIELD), CN3.P$3 (SHIELD), CN3.P$4 (SHIELD), CN3.P$6 (SHIELD), CN3.P$8 (SHIELD), CN3.P$10 (SHIELD), CN3.P$12 (SHIELD), CN3.SHEILD2 (SHIELD), CN3.SHIELD, CN3.SHIELD3 (SHIELD), CN3.SHIELD4 (SHIELD), D3.C, R4.1, R7.1, R8.1, R9.2, R13.2, U1.P$1 (NC(GND)), U1.P$3 (VSS), U1.P$13 (BS1), U1.P$30 (NC(GND)), U2.2 (GND), U3.2 (GND), U4.1 (GND), U6.2 (VSS), X1.9 (GND), Y2.2 (GND), Y2.4 (GND)
GPIO0: Q2.3 (C), R12.1, X1.12 (GPIO0)
IREF: R4.2, U1.P$9 (IREF)
MOSI/DATA1: U1.P$18 (D1/SDIN), X1.7 (GPIO13)
unnamed: CHG.C, R1.1
unnamed: C4.1, U1.P$5 (VDD)
unnamed: R1.2, U6.1 (STAT)
unnamed: D2.A, L1.P$2 (2), U3.1 (SW)
unnamed: R5.2, U1.P$26 (VSL)
unnamed: D1.A, R5.1
unnamed: C8.2, R6.1, R7.2, U3.3 (FB)
unnamed: R9.1, U6.5 (PROG)
unnamed: C14.2, U4.8 (XO), Y2.3 (2)
unnamed: D1.C, D3.A
unnamed: C9.2, U4.7 (XI), Y2.1
unnamed: Q1.1 (B), R2.2
unnamed: Q2.1 (B), R3.2
unnamed: R13.1, X1.10 (GPIO15)
unnamed: D5.A, S1.2
OLED_BS0: R8.2, U1.P$14 (BS0)
OLED_CS: U1.P$12 (CS#), X1.4 (GPIO16)
OLED_DC: U1.P$11 (D/C#), X1.14 (GPIO4)
OLED_RES: U1.P$10 (RES#), X1.13 (GPIO5)
RESET: Q1.3 (C), R11.2, X1.1 (RESET)
RTS: Q1.2 (E), R3.1, U4.14 (!RTS)
RX: U4.2 (TXD), X1.15 (RXD)
SCK/DATA0: U1.P$17 (D0/SCK), X1.5 (GPIO14)
TX: U4.3 (RXD), X1.16 (TXD)
V3: C16.1, U4.4 (V3)
VBAT: C13.1, CN2.1, S1.3 (S), U6.3 (VBAT)
VBUS: C6.1, C12.1, CHG.A, CN3.VBUS, D5.C, U2.1 (IN), U2.3 (EN), U6.4 (VDD)
VCC: C17.1, U4.16 (VCC)
VCOMH: C2.1, U1.P$28 (VCOMH)

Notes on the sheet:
3.3V Regulation
VOUT = 1.23V * (1 + R6/R7)
VOUT = 13.53V
This is 0.5V above the recommended voltage,
but uses common resistors for easy assembly
13V Boost
R4 = (VCC-6V)/12.5uA
= (13.5-6)/.0000125
= 600K
D1+D3 must be >= 1.4V
VDD generated
internally
10K = 100mA
5.0K = 200mA
2.0K = 500mA
1.0K = 1000mA

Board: 2 copper layers, 46 parts (12 on the bottom side), 40 nets, no tracks yet.

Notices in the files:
parts and their libraries:
microbuilder: This work is placed in the public domain, and may be freely used for commercial and non-commercial work with the following conditions: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
SparkFun-RF: Licensing: Creative Commons ShareAlike 4.0 International - https://creativecommons.org/licenses/by-sa/4.0
